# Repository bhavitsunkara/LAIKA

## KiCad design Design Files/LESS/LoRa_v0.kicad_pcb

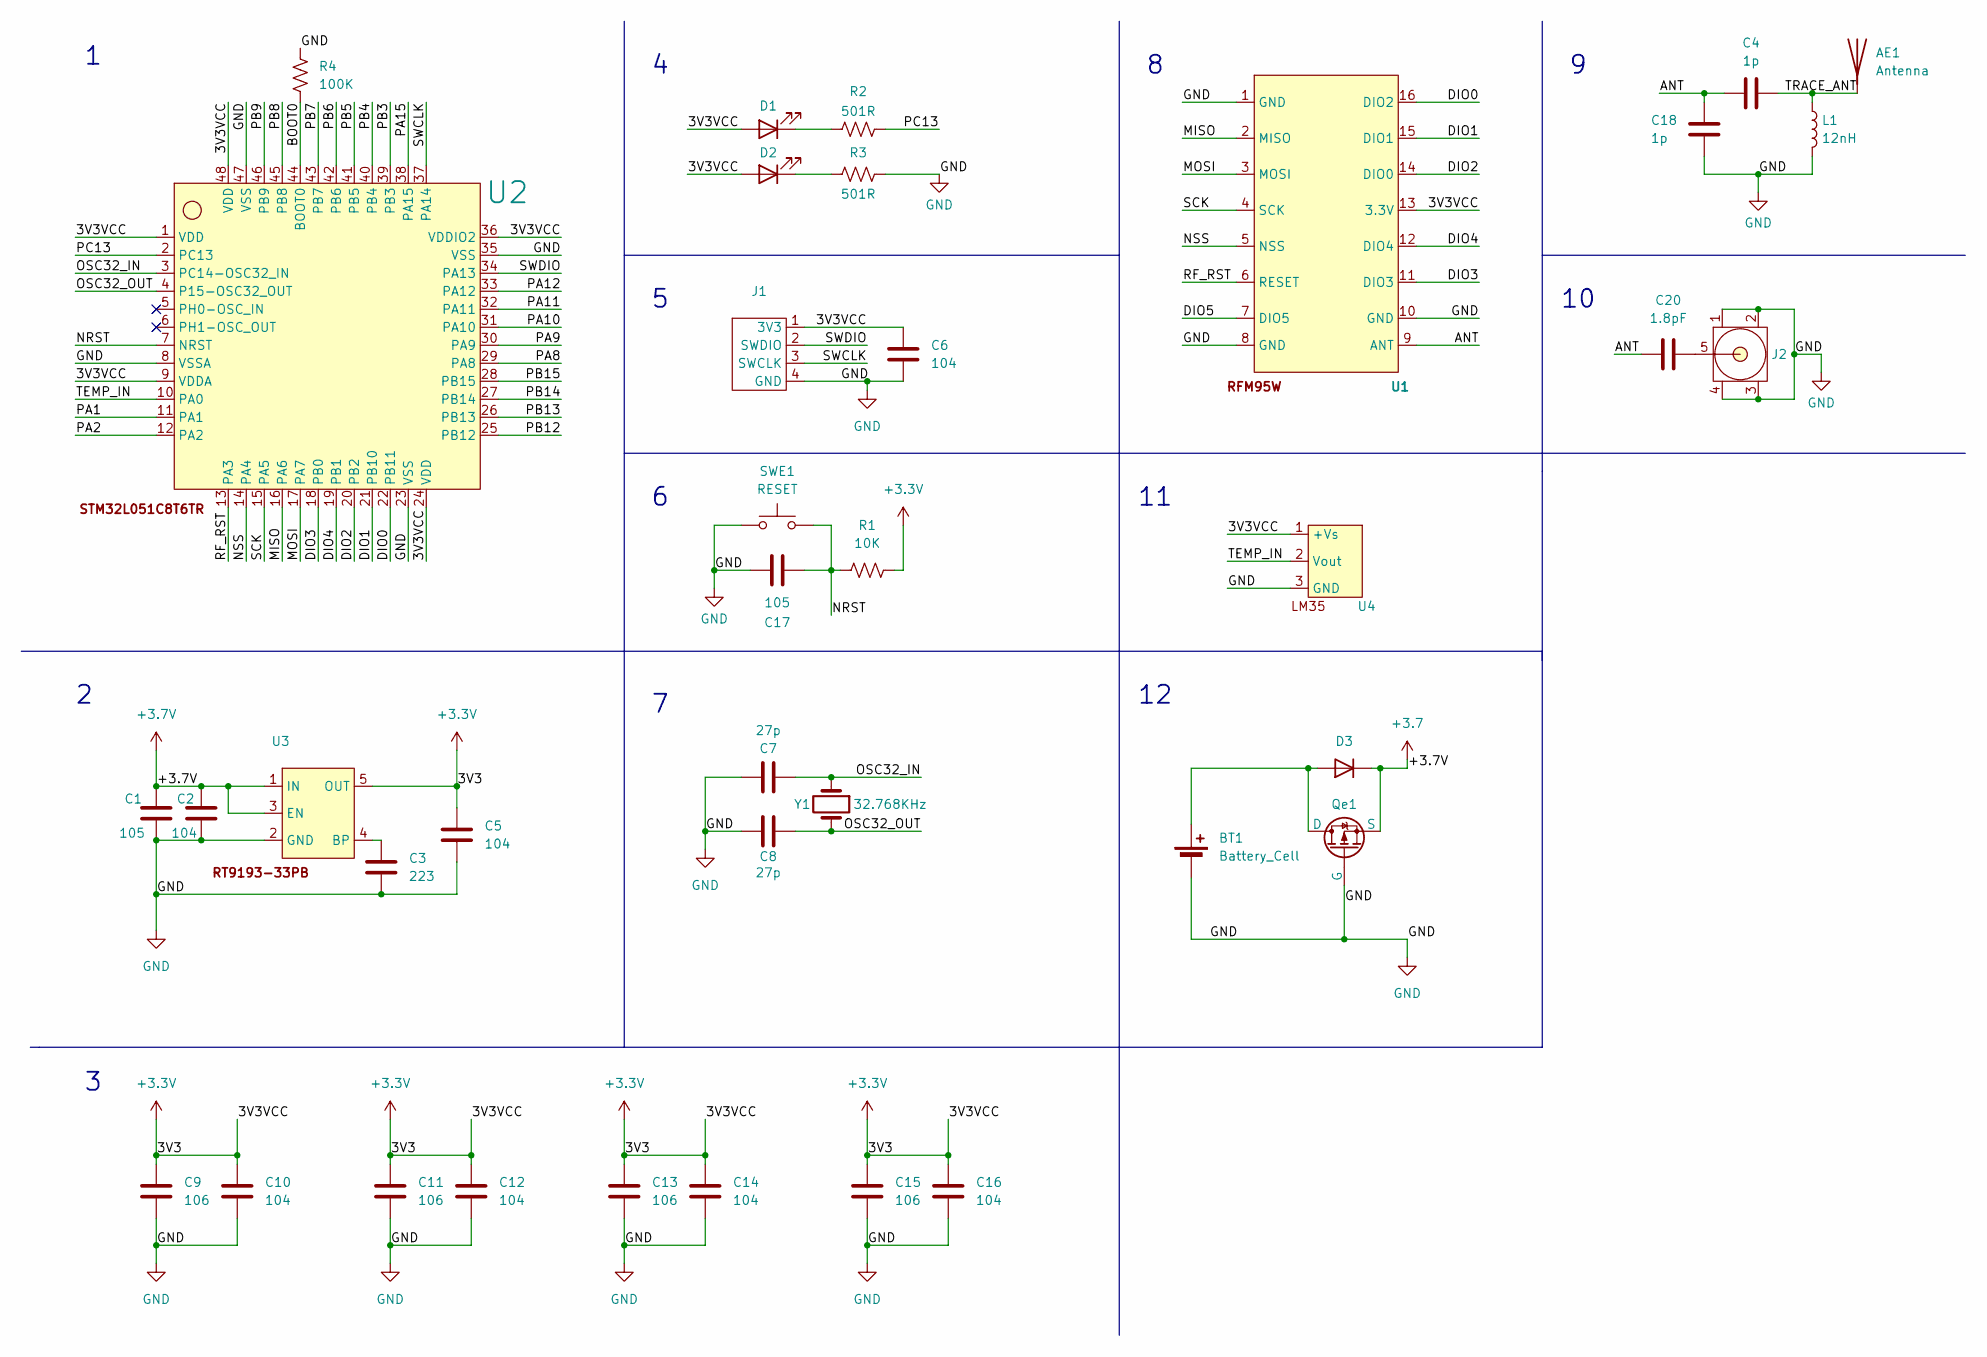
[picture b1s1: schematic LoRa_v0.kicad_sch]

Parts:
AE1: Antenna; 868-915MHz_PCB_ANT
BT1: Battery_Cell; Li-Ion_Battery
C1, C17: 105; C_0805_2012Metric_Pad1.18x1.45mm_HandSolder
C2, C5, C6, C10, C12, C14, C16: 104; C_0805_2012Metric_Pad1.18x1.45mm_HandSolder
C3: 223; C_0805_2012Metric_Pad1.18x1.45mm_HandSolder
C4, C18: 1p; C_0805_2012Metric_Pad1.18x1.45mm_HandSolder
C7, C8: 27p; C_0805_2012Metric_Pad1.18x1.45mm_HandSolder
C9, C11, C13, C15: 106; C_0805_2012Metric_Pad1.18x1.45mm_HandSolder
C20: 1.8pF; C_0805_2012Metric_Pad1.18x1.45mm_HandSolder
D1, D2: LED_0805_2012Metric_Pad1.15x1.40mm_HandSolder
D3: D_0805_2012Metric
J1: SWD_DEBUG
J2: SMA_COAX_RF_HEADER
L1: 12nH; L_0805_2012Metric_Pad1.05x1.20mm_HandSolder
Qe1: SOT-23_Handsoldering
R1: 10K; R_0805_2012Metric_Pad1.20x1.40mm_HandSolder
R2, R3: 501R; R_0805_2012Metric_Pad1.20x1.40mm_HandSolder
R4: 100K; R_0805_2012Metric_Pad1.20x1.40mm_HandSolder
SWE1: RESET; SW_DIP_SPSTx01_Slide_Copal_CHS-01B_W7.62mm_P1.27mm
U1: HOPERF_RFM9XW_SMD
U2: STM32L051C8T6TR
U3: SOT-23-5_HandSoldering
U4: LM35
Y1: 32.768KHz; C_1206_3216Metric_Pad1.33x1.80mm_HandSolder

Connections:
+3.3V: C5.1, C6.1, C9.1, C10.1, C11.1, C12.1, C13.1, C14.1, C15.1, C16.1, D1.2 (A), D2.2 (A), J1.1 (3V3), R1.2, U1.13 (3.3V), U2.1 (VDD), U2.9 (VDDA), U2.24 (VDD), U2.36 (VDDIO2), U2.48 (VDD), U3.5 (OUT), U4.1 (+Vs)
+3.7: C1.1, C2.1, D3.1 (K), Qe1.3 (S), U3.1 (IN), U3.3 (EN)
/BOOT0: R4.2, U2.44 (BOOT0)
/DIO0: U1.16 (DIO2), U2.22 (PB11)
/DIO1: U1.15 (DIO1), U2.21 (PB10)
/DIO2: U1.14 (DIO0), U2.20 (PB2)
/DIO3: U1.11 (DIO3), U2.18 (PB0)
/DIO4: U1.12 (DIO4), U2.19 (PB1)
/DIO5: U1.7 (DIO5)
/MISO: U1.2 (MISO), U2.16 (PA6)
/MOSI: U1.3 (MOSI), U2.17 (PA7)
/NRST: C17.1, R1.1, SWE1.2, U2.7 (NRST)
/NSS: U1.5 (NSS), U2.14 (PA4)
/OSC32_IN: C7.2, U2.3 (PC14-OSC32_IN), Y1.1
/OSC32_OUT: C8.2, U2.4 (P15-OSC32_OUT), Y1.2
/PA1: U2.11 (PA1)
/PA2: U2.12 (PA2)
/PA8: U2.29 (PA8)
/PA9: U2.30 (PA9)
/PA10: U2.31 (PA10)
/PA11: U2.32 (PA11)
/PA12: U2.33 (PA12)
/PA15: U2.38 (PA15)
/PB3: U2.39 (PB3)
/PB4: U2.40 (PB4)
/PB5: U2.41 (PB5)
/PB6: U2.42 (PB6)
/PB7: U2.43 (PB7)
/PB8: U2.45 (PB8)
/PB9: U2.46 (PB9)
/PB12: U2.25 (PB12)
/PB13: U2.26 (PB13)
/PB14: U2.27 (PB14)
/PB15: U2.28 (PB15)
/PC13: R2.2, U2.2 (PC13)
/RF_RST: U1.6 (RESET), U2.13 (PA3)
/SCK: U1.4 (SCK), U2.15 (PA5)
/SWCLK: J1.3 (SWCLK), U2.37 (PA14)
/SWDIO: J1.2 (SWDIO), U2.34 (PA13)
/TEMP_IN: U2.10 (PA0), U4.2 (Vout)
unnamed: BT1.1 (+), D3.2 (A), Qe1.1 (D)
unnamed: C20.2, J2.5
unnamed: D1.1 (K), R2.1
unnamed: D2.1 (K), R3.1
unnamed: C3.1, U3.4 (BP)

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
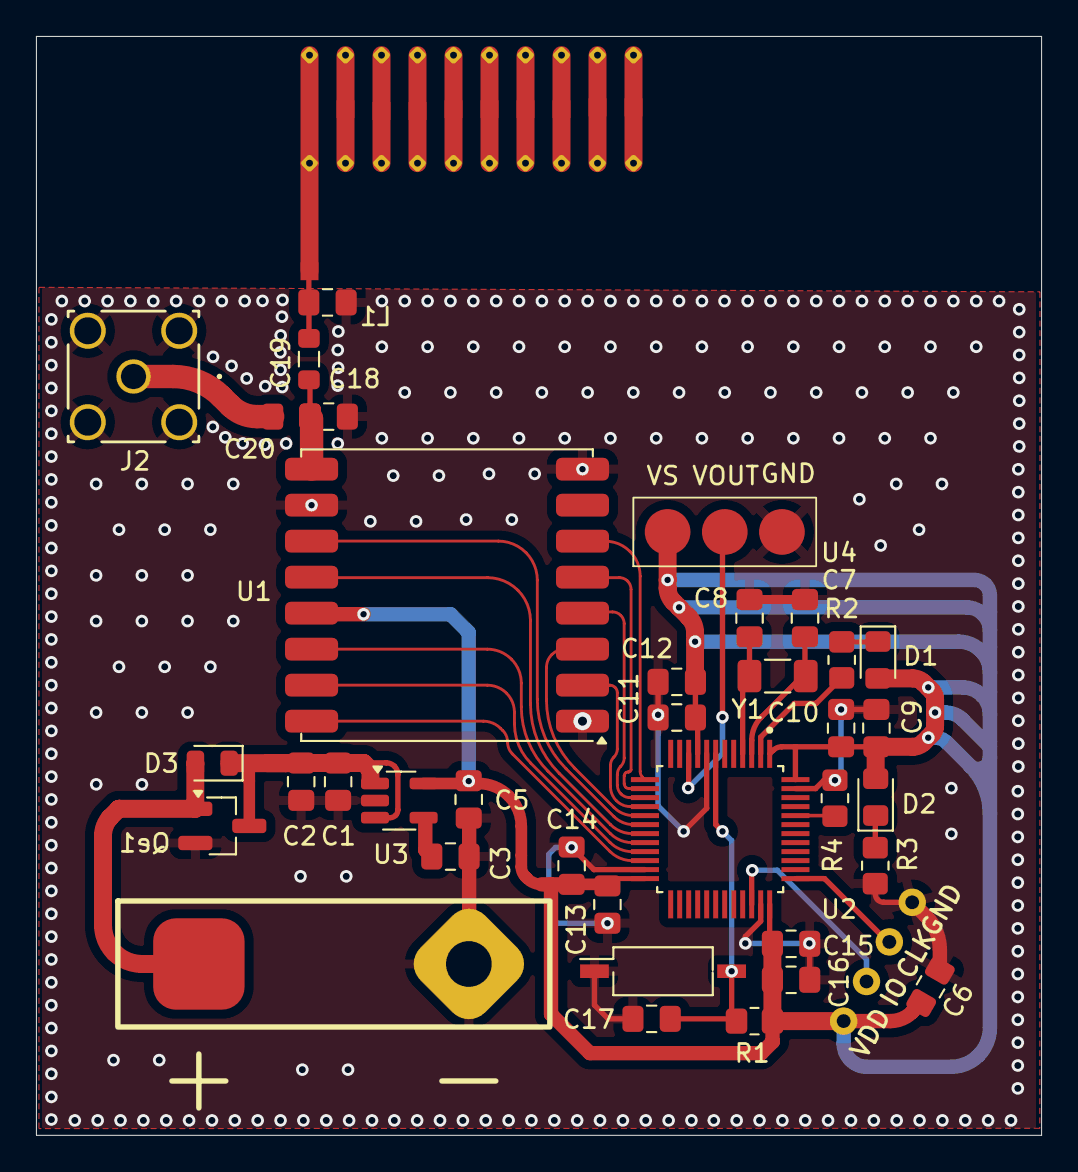
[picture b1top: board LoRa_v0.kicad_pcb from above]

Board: 2 copper layers, 55.8 x 61.0 mm, 38 parts (0 on the bottom side), 28 nets.

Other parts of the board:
A1: Antenna; 868-915MHz_PCB_ANT
C19: 1p; C_0805_2012Metric_Pad1.18x1.45mm_HandSolder

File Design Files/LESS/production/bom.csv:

Designator,Footprint,Quantity,Value,LCSC Part #
A1,868-915MHz_PCB_ANT,1,Antenna,
BT1,Li-Ion_Battery,1,Battery_Cell,
"C1, C17",0805,2,105,
"C10, C12, C14, C16, C2, C5, C6",0805,7,104,
"C11, C13, C15, C9",0805,4,106,
"C18, C19",0805,2,1p,
C20,0805,1,1.8pF,
C3,0805,1,223,
"C7, C8",0805,2,27p,
"D1, D2, D3",0805,3,~,
J1,SWD_DEBUG,1,~,
J2,SMA_COAX_RF_HEADER,1,~,
L1,0805,1,12nH,
QE1,SOT-23_Handsoldering,1,~,
R1,0805,1,10K,
"R2, R3",0805,2,501R,
R4,0805,1,100K,
SWE1,SW_DIP_SPSTx01_Slide_Copal_CHS-01B_W7.62mm_P1.27mm,1,RESET,
U1,HOPERF_RFM9XW_SMD,1,~,
U2,STM32L051C8T6TR,1,~,
U3,SOT-23-5_HandSoldering,1,~,
U4,LM35,1,~,
Y1,1206,1,32.768KHz,

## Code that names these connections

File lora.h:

#ifndef LORA_H
#define LORA_H

#ifdef __cplusplus
extern C {
#endif

#include "main.h"

// registers
#define REG_FIFO                 0x00
#define REG_OP_MODE              0x01
#define REG_FRF_MSB              0x06
#define REG_FRF_MID              0x07
#define REG_FRF_LSB              0x08
#define REG_PA_CONFIG            0x09
#define REG_OCP                  0x0b
#define REG_LNA                  0x0c
#define REG_FIFO_ADDR_PTR        0x0d
#define REG_FIFO_TX_BASE_ADDR    0x0e
#define REG_FIFO_RX_BASE_ADDR    0x0f
#define REG_FIFO_RX_CURRENT_ADDR 0x10
#define REG_IRQ_FLAGS            0x12
#define REG_RX_NB_BYTES          0x13
#define REG_PKT_SNR_VALUE        0x19
#define REG_PKT_RSSI_VALUE       0x1a
#define REG_RSSI_VALUE           0x1b
#define REG_MODEM_CONFIG_1       0x1d
#define REG_MODEM_CONFIG_2       0x1e
#define REG_PREAMBLE_MSB         0x20
#define REG_PREAMBLE_LSB         0x21
#define REG_PAYLOAD_LENGTH       0x22
#define REG_MODEM_CONFIG_3       0x26
#define REG_FREQ_ERROR_MSB       0x28
#define REG_FREQ_ERROR_MID       0x29
#define REG_FREQ_ERROR_LSB       0x2a
#define REG_RSSI_WIDEBAND        0x2c
#define REG_DETECTION_OPTIMIZE   0x31
#define REG_INVERTIQ             0x33
#define REG_DETECTION_THRESHOLD  0x37
#define REG_SYNC_WORD            0x39
#define REG_INVERTIQ2            0x3b
#define REG_DIO_MAPPING_1        0x40
#define REG_VERSION              0x42
#define REG_PA_DAC               0x4d

// modes
#define MODE_LONG_RANGE_MODE     0x80
#define MODE_SLEEP               0x00
#define MODE_STDBY               0x01
#define MODE_TX                  0x03
#define MODE_RX_CONTINUOUS       0x05
#define MODE_RX_SINGLE           0x06

// IRQ Flags
#define MODE_TX_DONE							0x08
#define MODE_RX_DONE							0x40
#define MODE_CRC_ERROR						0x20
#define MODE_RX_TIMEOUT           0x80

#define RF_MID_BAND_THRESHOLD    	525E6
#define RSSI_OFFSET_HF_PORT      	157
#define RSSI_OFFSET_LF_PORT      	164

// PA Config 
#define PA_BOOST									0x80

#define MAX_PKT_LENGTH           255

// Common frequencies (in Hz)
#define FREQ_433_MHZ               433000000
#define FREQ_868_MHZ               868000000
#define FREQ_915_MHZ               915000000

// Pin definitions for SPI1
#define LORA_NSS_PIN               0x00000004  // PA4
#define LORA_SCK_PIN               0x00000005  // PA5
#define LORA_MISO_PIN              0x00000006  // PA6
#define LORA_MOSI_PIN              0x00000007  // PA7
#define LORA_RESET_PIN             0x00000003  // PA3

// Function prototypes
// public
void spi_init(void);

void lora_reset(void);

void lora_write_reg(uint8_t reg, uint8_t value);
uint8_t lora_read_reg(uint8_t reg);

uint8_t begin(uint32_t frequency);
void end();

uint8_t beginPacket(uint8_t implicitHeader); 	// implcitHeader = 0
uint8_t endPacket();							

uint8_t parsePacket(uint8_t size);
uint16_t packetRssi();
float packetSnt();
long packetFrequencyError();

int rssi();

// from print in cpp
uint8_t write(const uint8_t *buffer, uint8_t size);
 
// from stream in cpp
int available();
int read();
int peek();

void idle();
void sleep();

void setTxPower(uint8_t level);
void setFrequency(uint32_t frequency);
void setSpreadingFactor(uint8_t sf);
long getSignalBandwidth();
void setSignalBandwidth(uint32_t sbw);
void setCodingRate4(uint8_t denominator);
void setPreambleLength(long length);
void setSyncWord(int sw);
void enableCrc();
void disableCrc();
void enableInvertIQ();
void disableInvertIQ();

void setOCP(uint8_t mA); 		// Over current protection
void setGain(uint8_t gain);

uint8_t random();

//private
void explicitHeaderMode();
void implicitHeaderMode();

//void handleDio0Rise();
bool isTransmitting();

uint8_t getSpreadingFactor();
long getSignalBandwidth();

void setLdoFlag();

#ifdef __cplusplus
}
#endif

#endif /* LORA_H */

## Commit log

2024-11-25 Core files and flash code.
2024-11-27 Finalized Rev A firmware version 0.1 for the LESS Project
2024-11-27 fixed typo
2024-11-27 Added all the required files to reproduce and further develop the project
2024-11-27 fixing push issue
2024-11-27 Added custom footprints
